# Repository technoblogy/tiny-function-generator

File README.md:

# Tiny Function Generator
A signal generator based on an ATtiny85 that uses Direct Digital Synthesis to generate a range of different waveforms, including sine, square, triangle, and noise. See http://www.technoblogy.com/show?2FCL.

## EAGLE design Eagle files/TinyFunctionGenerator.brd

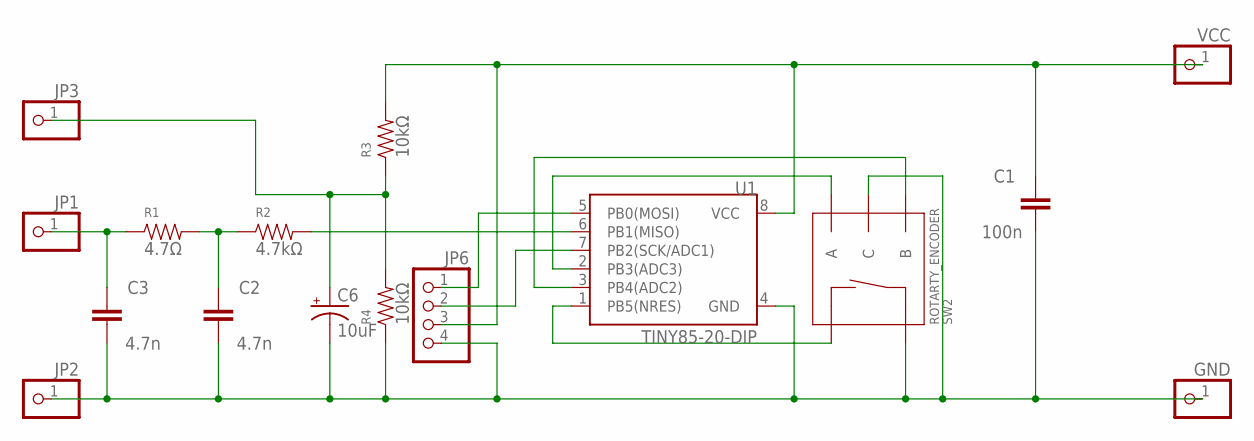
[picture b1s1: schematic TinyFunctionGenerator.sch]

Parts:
C1: 100n; AXIAL-5MM
C2, C3: 4.7n; CAP-PTH-SMALL
C6: 10uF; CPOL-RADIAL-10UF-25V
GND: PINHD-1X1CB; 1X01-CLEANBIG
JP1, JP2, JP3: PINHD-1X1CB; 1X01-CLEANBIG
JP6: HEADER-1X4ROUND; 1X04_ROUND
R1: 4.7Ω; AXIAL-0.4
R2: 4.7kΩ; AXIAL-0.4
R3, R4: 10kΩ; AXIAL-0.4
SW2: ROTARTY_ENCODER; ROTARY_ENC_PLAIN
U1: TINY85-20-DIP; DIP08
VCC: PINHD-1X1CB; 1X01-CLEANBIG

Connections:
GND: C1.P$2 (2), C2.2, C3.2, C6.2 (-), GND.1, JP2.1, JP6.4, R4.P$1 (1), SW2.C, SW2.SW+, U1.4 (GND)
unnamed: JP6.2, U1.7 (PB2(SCK/ADC1))
unnamed: JP6.1, U1.5 (PB0(MOSI))
unnamed: C2.1, R1.P$2 (2), R2.P$1 (1)
unnamed: R2.P$2 (2), U1.6 (PB1(MISO))
unnamed: SW2.A, U1.2 (PB3(ADC3))
unnamed: SW2.B, U1.3 (PB4(ADC2))
unnamed: SW2.SW-, U1.1 (PB5(NRES))
unnamed: C3.1, JP1.1, R1.P$1 (1)
unnamed: C6.1 (+), JP3.1, R3.P$1 (1), R4.P$2 (2)
VCC: C1.P$1 (1), JP6.3, R3.P$2 (2), U1.8 (VCC), VCC.1

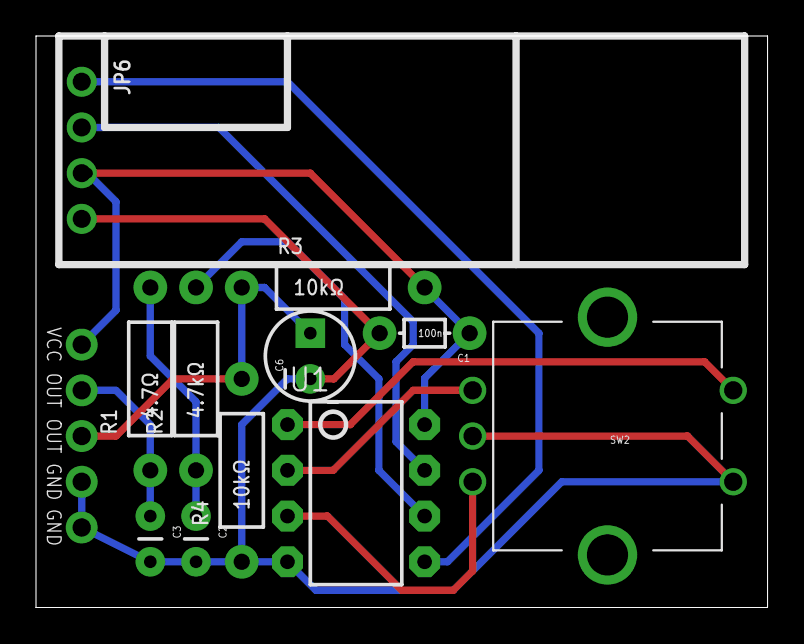
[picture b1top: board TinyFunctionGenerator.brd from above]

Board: 2 copper layers, 40.6 x 31.8 mm, 16 parts (0 on the bottom side), 11 nets.

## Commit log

2019-02-07 Version 1 - 7th February 2019
2019-09-24 Correct comment
2019-09-24 Delete

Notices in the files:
parts and their libraries:
SparkFun-Electromechanical: Licensing: Creative Commons ShareAlike 4.0 International - https://creativecommons.org/licenses/by-sa/4.0
microbuilder: This work is placed in the public domain, and may be freely used for commercial and non-commercial work with the following conditions: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
